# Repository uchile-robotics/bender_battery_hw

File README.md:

# bender_battery_hw
Bender Battery Managment and Distribution KiCad files

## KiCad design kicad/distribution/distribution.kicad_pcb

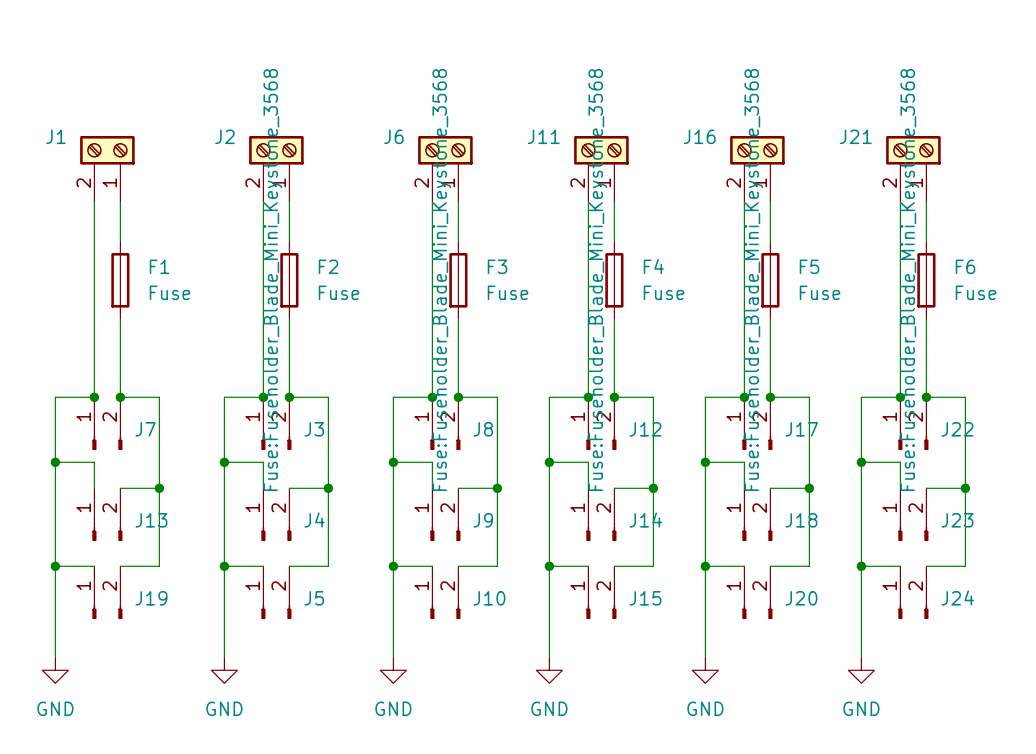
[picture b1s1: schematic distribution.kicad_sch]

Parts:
F1, F2, F3, F4, F5, F6: Fuse; Fuseholder_Blade_Mini_Keystone_3568
J1, J2, J6, J11, J16, J21: Screw_Terminal_01x02; TerminalBlock_Phoenix_PT-1,5-2-5.0-H_1x02_P5.00mm_Horizontal
J3, J4, J5, J7, J8, J9, J10, J12, J13, J14, J15, J17, J18, J19, J20, J22, J23, J24: Conn_01x02_Pin; AMASS_XT60-M_1x02_P7.20mm_Vertical

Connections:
GND: J1.2, J2.2, J3.1, J4.1, J5.1, J6.2, J7.1, J8.1, J9.1, J10.1, J11.2, J12.1, J13.1, J14.1, J15.1, J16.2, J17.1, J18.1, J19.1, J20.1, J21.2, J22.1, J23.1, J24.1
unnamed: F1.1, J1.1
unnamed: F2.1, J2.1
unnamed: F2.2, J3.2, J4.2, J5.2
unnamed: F3.1, J6.1
unnamed: F3.2, J8.2, J9.2, J10.2
unnamed: F4.1, J11.1
unnamed: F4.2, J12.2, J14.2, J15.2
unnamed: F1.2, J7.2, J13.2, J19.2
unnamed: F5.1, J16.1
unnamed: F5.2, J17.2, J18.2, J20.2
unnamed: F6.1, J21.1
unnamed: F6.2, J22.2, J23.2, J24.2

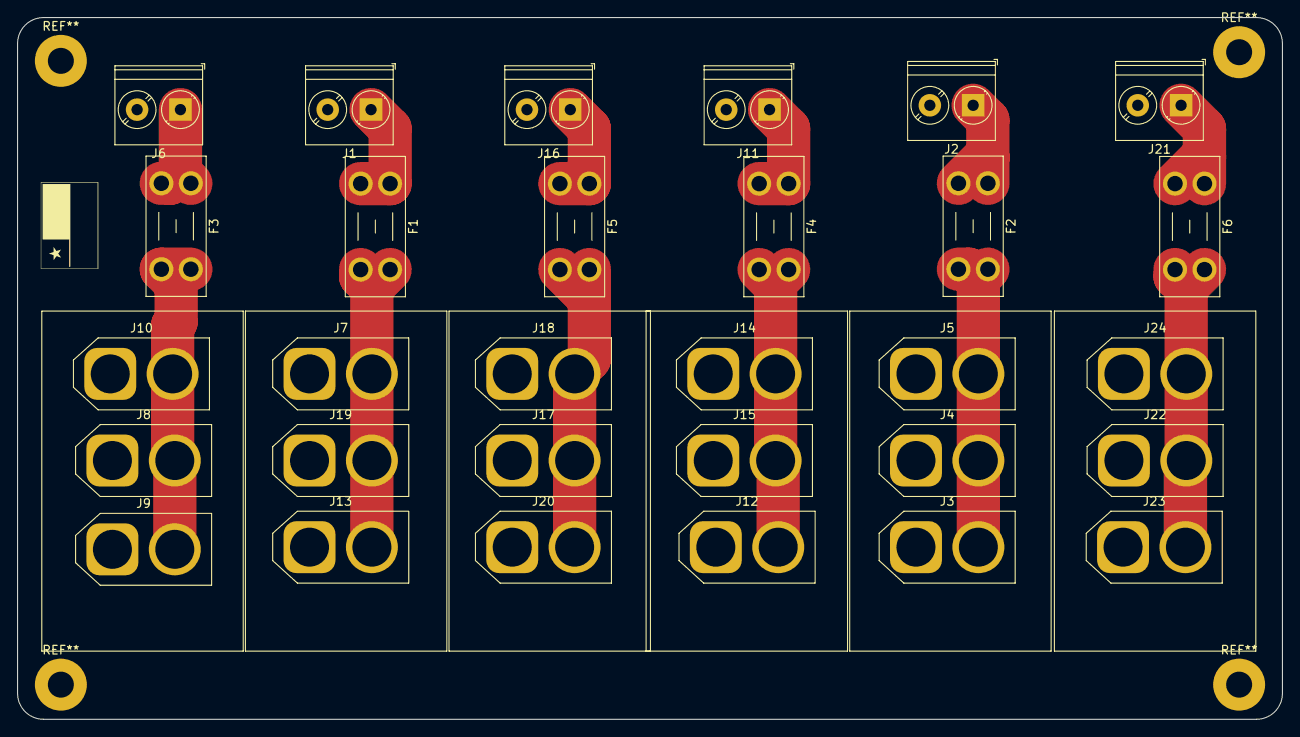
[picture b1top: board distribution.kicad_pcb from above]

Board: 2 copper layers, 146.0 x 81.0 mm, 30 parts (0 on the bottom side), 13 nets.

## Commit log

2025-08-17 Add distribution board files
